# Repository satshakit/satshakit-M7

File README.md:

<div align="center"><h1 style="font-family: courier;" align="center">satshakit-M7</h1></div>

<div align="center"></div>
<div align="center"><i>An open source & fabbable STM32F7 microcontroller board.</i></div>

Premises
--
My personal objective with the development of satshakit-M7 is to bring forward the current possibilities of a Fab Lab to, locally and at cheap price, produce and customize powerful and advanced microcontroller boards, like the ones used in production. Satshakit-M7 is embedding one of the tops chips today available on the market at the time of writing (2018), aiming to represent the state of the art of what you can produce by yourself versus what you can buy. The board was made with a cheap and small milling machine and a traditional soldering station, for a total equipment price of 300€ paid once, if you mind that producing such board will cost you a lot. I personally believe that one day we will (almost) build everything we need in a Fab Lab, and satshakit-M7 wants to be a step further in that direction.

The board
--
satshakit-M7 embeds a **[Cortex M7](https://developer.arm.com/products/processors/cortex-m/cortex-m7)** microcontroller, produced by STMicroelectronics the: **[STM32F765VIT6](http://www.st.com/en/microcontrollers/stm32f765vi.html)**. Among others, the **[STM32F7](http://www.st.com/en/microcontrollers/stm32f7-series.html?querycriteria=productId=SS1858)** chip line and the Cortex-M7 architecture are including the following features:

- **32 bit** architecture
- **6-stage superscalar** pipeline with branch prediction
- dedicated **DSP** instructions
- **hardware acceleration** for graphic computation

satshakit-M7 **schematic**:

Furthermore, as the STM32 architecture and pinout are quite similar among the different STM32FXX, you could reuse the satshakit-M7 design to host other STM32F microcontrollers. Satshakit-M7 is designed to be one simple, yet complete, PCB to tryout most of the STM32F765VIT6 features and I/O. Apart from the microcontroller itself and few other small parts, the rest is having 1206 components and quite enough space to ensure an easy soldering. 

Here the main **tech specs** of satshakit-M7:

- operating frequency up to **216mhz**
- flash memory of **2MB**
- ram memory of **512KB**
- **QUAD-SPI** memory interface supporting up to 4GB of DDR external ram
- Mini **USB 2.0** full speed support with different modes (DFU,OTG,AUDIO..)
- 3 x **12bit** ADCs
- general purpose **DMA**
- camera interface up to **54MB/s**
- **4** x serials
- **4** x I2C
- **3** x CANs
- **full pinout** on board
- **HDMI-CEC**
- **LCD TFT** controller
- working voltage of **3.3V**
- cost of **21€** (buying from digi-key per single board, way less for more or from China)

satshakit-M7 **board**:

In comparison to the old **[satshakit](https://github.com/satshakit/satshakit)** based on the 328P, satshakit-M7 is several times faster and having much more memory. Here some numbers about it:

- **13.5** times higher operating frequency
- **256** times more ram memory
- **64** times more flash memory
- about **3** times more I/O pins 

Downloads
--

**downloads (right click download as):**

- [satshakit-M7 schematic](https://github.com/satshakit/satshakit-M7/raw/master/eagle/satshakit-M7/satshakit-M7.sch)
- [satshakit-M7 board](https://github.com/satshakit/satshakit-M7/raw/master/eagle/satshakit-M7/satshakit-M7.brd)
- [satshakit-M7 internal traces png](https://github.com/satshakit/satshakit-M7/raw/master/media/satshakit-M7-internal.png)
- [satshakit-M7 cutout png](https://github.com/satshakit/satshakit-M7/raw/master/media/satshakit-M7-cutout.png)
- [satshakit-M7 BOM ods](https://github.com/satshakit/satshakit-M7/raw/master/docs/satshakit-M7-BOM.ods)
- [satshakit-M7 BOM xlsx](https://github.com/satshakit/satshakit-M7/raw/master/docs/satshakit-M7-BOM.xlsx)
- [satshakit-M7 216mhz USB CubeMX example](https://github.com/satshakit/satshakit-M7/raw/master/examples/satshakit-M7-usb-216mhz.zip)
- [satshakit-M7 blink SW4STM32 example](https://github.com/satshakit/satshakit-M7/raw/master/examples/test_blink.zip)

Milling and soldering tips
--

To mill the board a **0.1mm chamfer tool** was used. I recommend to buy several of these as they could warn off  quickly, and they are very easy to be damaged (eg if you drop them). The ones from China usually lasts few cuts, better the one from USA/Europe but of course more expensive.

With such tools you should ensure to have a **flat copper sheet** and therefore also a **flat bed**. In case some parts are not milled properly you can relaunch only a specific areas by cropping subsections of the PNG. To make the board here 2 jobs were necessary. Another solution would be to launch only the job to engrave the traces of the microntroller with the 0.1mm tool, and then launch the rest with a traditional 0.4mm tool (1/64th).

Solder the microntroller by deploying an **huge amount of soldering on the sides** as shown here:

and then by removing it **using a desoldering trace**.

Make sure to **strongly solder the USB connector** to avoid that it will easily detach while connecting and disconnecting the USB cable.

Please make sure that all the **connections are fine** by using the testing function of a multimeter before powering the board. More **patience in testing** will be rewarding is then you have to trash all the board for a mistake. Also, use an **USB hub** for the first smoke test to avoid eventually damage your computer. 

Getting started with satshakit-M7
--

Find below the **satshakit-M7 pinout**:

To have a look to more functionalities associated with each pin please have into the **[STM32F765VIT6 datasheet](http://www.st.com/content/ccc/resource/technical/document/datasheet/group3/c5/37/9c/1d/a6/09/4e/1a/DM00273119/files/DM00273119.pdf/jcr:content/translations/en.DM00273119.pdf)**.

In order to program the satshakit-M7, it is recommended to use a programmer called **ST-Link v2**. You can buy the original on **[digi-key](https://www.digikey.de/product-detail/en/stmicroelectronics/ST-LINK-V2/497-10484-ND/2214535)** or a chinese clone for much less on ebay or on **[Banggood](https://www.digikey.de/product-detail/en/stmicroelectronics/ST-LINK-V2/497-10484-ND/2214535)**.

When you program the satshakit-M7, it is always recommended to:

- connect the **boot pin to the 3.3V VCC** to ensure that the programming pins are not already used for something else
- avoid to power the board from the programmer itself and connect an **external 3.3V power source**

Find here the **connection schema to program** the satshakit-M7:

To program the satshakit-M7 using the ST-Link v2 you download and install the **[STM32 ST-LINK utility ](http://www.st.com/en/development-tools/stsw-link004.html)**, which also installs the ST-Link drivers.

To program the board follow the steps below:

1. connect the satshakit-M7 following the above schema
2. connect the ST-Link to the USB of your PC
3. open the STM32 ST-LINK utility
4. click on target->connect
5. at this point if there's an error the software will warn you, in this case double check the connections and try again
6. if the connection it's ok, click on target->program
7. browse to load you binary file
8. eventually change some options, eg to verify the flash
8. press start
9. wait for the program to be uploaded
10. disconnect the board 
11. remove the boot jumper
12. power again your board

Other useful things can be found in the target menu. Try to **update your ST Link firmware** in ST_LINK->update firmware in case you have other problems in uploading the files. For more info please look at the **[STM32 ST-LINK manual](http://www.st.com/content/ccc/resource/technical/document/user_manual/65/e0/44/72/9e/34/41/8d/DM00026748.pdf/files/DM00026748.pdf/jcr:content/translations/en.DM00026748.pdf)** and the **[ST-LINK Utility manual](http://www.st.com/content/ccc/resource/technical/document/user_manual/e6/10/d8/80/d6/1d/4a/f2/CD00262073.pdf/files/CD00262073.pdf/jcr:content/translations/en.CD00262073.pdf)**.

The STM32F765VIT6 can be easiliy be configured using a graphical tool from ST, the **[STM32CubeMX](http://www.st.com/en/development-tools/stm32cubemx.html)**. Generally this is the first step to understand the main functionalities of the chips, and it's needed to generate the base code of your programs that you can later on use in your IDE. If you wish to use it, I created an **example project in the downloads: [216-USB](examples/satshakit-M7-usb-216mhz.zip)**. which you can use to run the satshakit-M7 at 216mhz and to enable the USB port in VCP mode.

When you generate the base code with STM32CubeMX, you can specify the kind of IDE you will use later to write on top of it your own code. I recommend to use the **[SW4STM32](http://www.openstm32.org/HomePage)** IDE, which is based on eclipse. I added an **example project made with this ide in the downloads: [test-blink](examples/test_blink.zip)**.

Media
--

satshakit-M7 pictures:

satshakit-M7 connected with the programmer:

satshakit-M7 with the first prototype:

satshakit-M7 blinks:

Author
--

- Daniele Ingrassia

Contact
--
- **ingrassiada@gmail.com**
- **[linkedin](http://it.linkedin.com/in/danieleingrassia)**

Thanks
--
[Fablab Kamp-Lintfort](http://fablab.hochschule-rhein-waal.de/index.php/de/)<br />
Hochschule Rhein-Waal<br />
Friedrich-Heinrich-Allee 25, 47475 Kamp-Lintfort, Germany<br />
fablab@hochschule-rhein-waal.de

License
--
This work is licensed under the terms of the open source license: Creative Commons Attribution-ShareAlike 4.0 International ([CC BY-SA 4.0](https://creativecommons.org/licenses/by-sa/4.0/)).

Disclaimer  
--

<div class="align-justify">
This hardware/software is provided "as is", and you use the hardware/software at your own risk. Under no circumstances shall any author be liable for direct, indirect, special, incidental, or consequential damages resulting from the use, misuse, or inability to use this hardware/software, even if the authors have been advised of the possibility of such damages.</div>

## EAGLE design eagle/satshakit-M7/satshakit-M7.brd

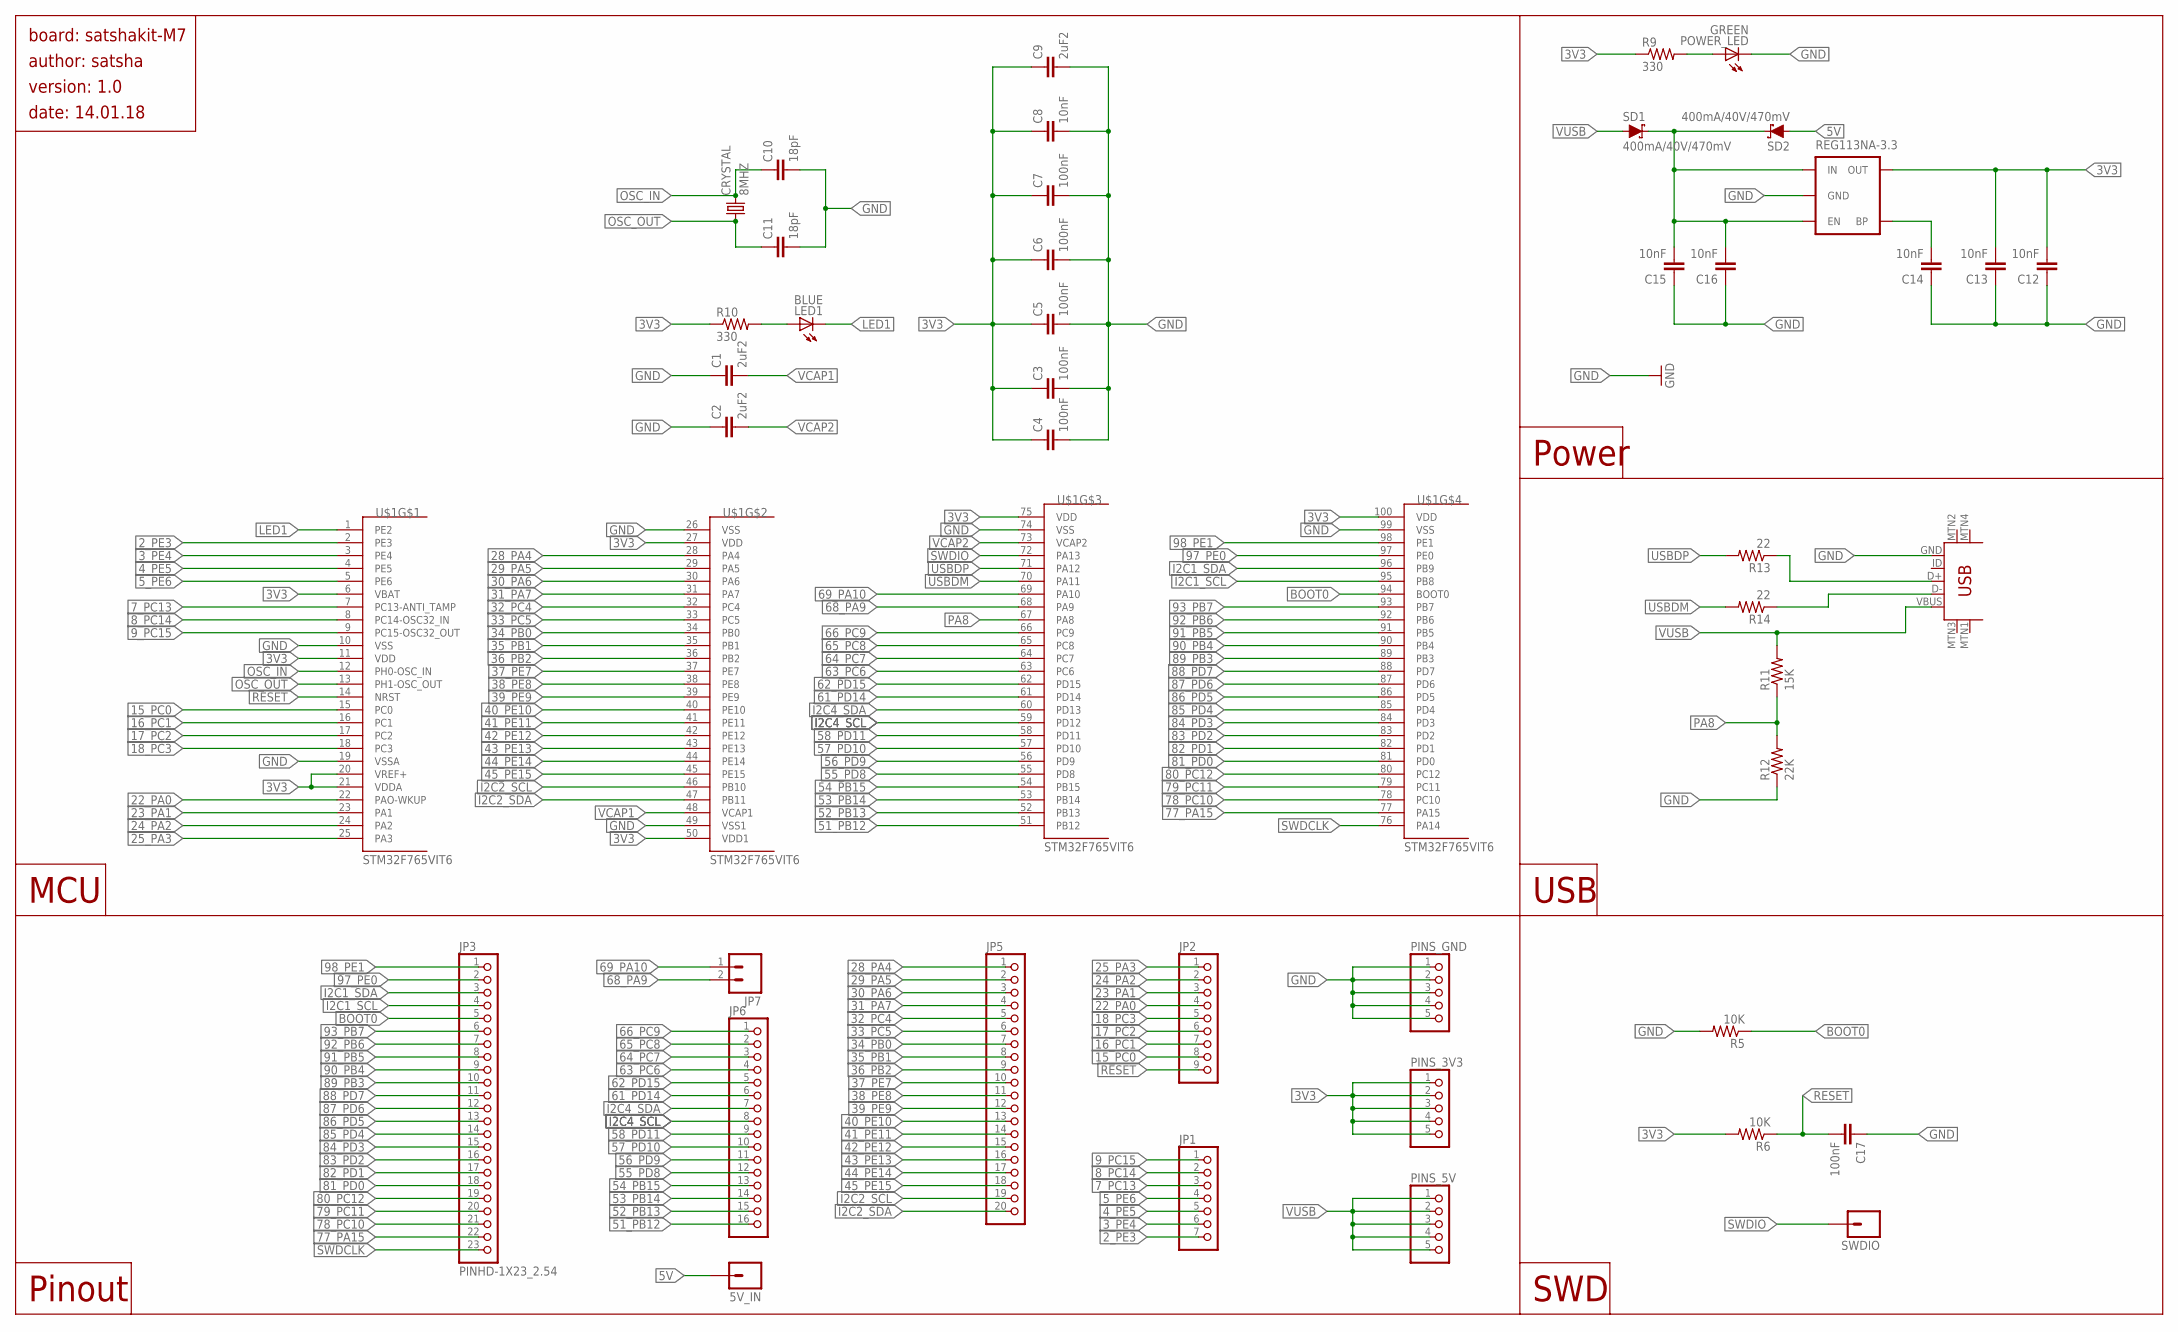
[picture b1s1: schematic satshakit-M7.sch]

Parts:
5V_IN: M01PTH_LONGPAD; 1X01_LONGPAD
C1, C2, C9: 2uF2; 1206
C3, C4, C5, C6, C7, C17: 100nF; 1206
C8, C12, C13, C14, C15, C16: 10nF; 1206
C10, C11: 18pF; 1206
CRYSTAL: 8MHZ; CSM-7X-DU
JP1: PINHD-1X07_2.54; 1X07
JP2: PINHD-1X09_2.54; 1X09
JP3: PINHD-1X23_2.54; 1X23
JP5: PINHD-1X20_2.54; 1X20
JP6: PINHD-1X16_2.54; 1X16
JP7: M02; 1X02_LONGPADS
LED1: BLUE; 1206
PINS_3V3, PINS_5V: PINHD-1X05_2.54; 1X05
PINS_GND: PINHD-1X05_2.54; 1X05
POWER_LED: GREEN; 1206
R5, R6: 10K; 1206
R9, R10: 330; 1206
R11: 15K; 1206
R12: 22K; 1206
R13, R14: 22; 1206
REG113NA-3.3: V_REG_LDOSMD; SOT23-5
SD1, SD2: 400mA/40V/470mV; SOT23-3
SWDIO: M01PTH_LONGPAD; 1X01_LONGPAD
U$1: STM32F765VIT6; LQFP100
U$7: USB-MINIB-5PIN; USB-MINIB

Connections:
2_PE3: JP1.7, U$1.2 (PE3)
3V3: C3.1, C4.1, C5.1, C6.1, C7.1, C8.1, C9.1, C12.2, C13.2, PINS_3V3.1, PINS_3V3.2, PINS_3V3.3, PINS_3V3.4, PINS_3V3.5, R6.2, R9.1, R10.1, REG113NA-3.3.5 (OUT), U$1.6 (VBAT), U$1.11 (VDD), U$1.20 (VREF+), U$1.21 (VDDA), U$1.27 (VDD), U$1.50 (VDD1), U$1.75 (VDD), U$1.100 (VDD)
3_PE4: JP1.6, U$1.3 (PE4)
4_PE5: JP1.5, U$1.4 (PE5)
5V: 5V_IN.1, SD2.1 (A)
5_PE6: JP1.4, U$1.5 (PE6)
7_PC13: JP1.3, U$1.7 (PC13-ANTI_TAMP)
8_PC14: JP1.2, U$1.8 (PC14-OSC32_IN)
9_PC15: JP1.1, U$1.9 (PC15-OSC32_OUT)
15_PC0: JP2.8, U$1.15 (PC0)
16_PC1: JP2.7, U$1.16 (PC1)
17_PC2: JP2.6, U$1.17 (PC2)
18_PC3: JP2.5, U$1.18 (PC3)
22_PA0: JP2.4, U$1.22 (PAO-WKUP)
23_PA1: JP2.3, U$1.23 (PA1)
24_PA2: JP2.2, U$1.24 (PA2)
25_PA3: JP2.1, U$1.25 (PA3)
28_PA4: JP5.1, U$1.28 (PA4)
29_PA5: JP5.2, U$1.29 (PA5)
30_PA6: JP5.3, U$1.30 (PA6)
31_PA7: JP5.4, U$1.31 (PA7)
32_PC4: JP5.5, U$1.32 (PC4)
33_PC5: JP5.6, U$1.33 (PC5)
34_PB0: JP5.7, U$1.34 (PB0)
35_PB1: JP5.8, U$1.35 (PB1)
36_PB2: JP5.9, U$1.36 (PB2)
37_PE7: JP5.10, U$1.37 (PE7)
38_PE8: JP5.11, U$1.38 (PE8)
39_PE9: JP5.12, U$1.39 (PE9)
40_PE10: JP5.13, U$1.40 (PE10)
41_PE11: JP5.14, U$1.41 (PE11)
42_PE12: JP5.15, U$1.42 (PE12)
43_PE13: JP5.16, U$1.43 (PE13)
44_PE14: JP5.17, U$1.44 (PE14)
45_PE15: JP5.18, U$1.45 (PE15)
51_PB12: JP6.16, U$1.51 (PB12)
52_PB13: JP6.15, U$1.52 (PB13)
53_PB14: JP6.14, U$1.53 (PB14)
54_PB15: JP6.13, U$1.54 (PB15)
55_PD8: JP6.12, U$1.55 (PD8)
56_PD9: JP6.11, U$1.56 (PD9)
57_PD10: JP6.10, U$1.57 (PD10)
58_PD11: JP6.9, U$1.58 (PD11)
61_PD14: JP6.6, U$1.61 (PD14)
62_PD15: JP6.5, U$1.62 (PD15)
63_PC6: JP6.4, U$1.63 (PC6)
64_PC7: JP6.3, U$1.64 (PC7)
65_PC8: JP6.2, U$1.65 (PC8)
66_PC9: JP6.1, U$1.66 (PC9)
68_PA9: JP7.2, U$1.68 (PA9)
69_PA10: JP7.1, U$1.69 (PA10)
77_PA15: JP3.22, U$1.77 (PA15)
78_PC10: JP3.21, U$1.78 (PC10)
79_PC11: JP3.20, U$1.79 (PC11)
80_PC12: JP3.19, U$1.80 (PC12)
81_PD0: JP3.18, U$1.81 (PD0)
82_PD1: JP3.17, U$1.82 (PD1)
83_PD2: JP3.16, U$1.83 (PD2)
84_PD3: JP3.15, U$1.84 (PD3)
85_PD4: JP3.14, U$1.85 (PD4)
86_PD5: JP3.13, U$1.86 (PD5)
87_PD6: JP3.12, U$1.87 (PD6)
88_PD7: JP3.11, U$1.88 (PD7)
89_PB3: JP3.10, U$1.89 (PB3)
90_PB4: JP3.9, U$1.90 (PB4)
91_PB5: JP3.8, U$1.91 (PB5)
92_PB6: JP3.7, U$1.92 (PB6)
93_PB7: JP3.6, U$1.93 (PB7)
97_PE0: JP3.2, U$1.97 (PE0)
98_PE1: JP3.1, U$1.98 (PE1)
BOOT0: JP3.5, R5.1, U$1.94 (BOOT0)
GND: C1.1, C2.1, C3.2, C4.2, C5.2, C6.2, C7.2, C8.2, C9.2, C10.2, C11.2, C12.1, C13.1, C14.1, C15.1, C16.1, C17.1, PINS_GND.1, PINS_GND.2, PINS_GND.3, PINS_GND.4, PINS_GND.5, POWER_LED.2 (C), R5.2, R12.1, REG113NA-3.3.2 (GND), U$1.10 (VSS), U$1.19 (VSSA), U$1.26 (VSS), U$1.49 (VSS1), U$1.74 (VSS), U$1.99 (VSS), U$7.GND
I2C1_SCL: JP3.4, U$1.95 (PB8)
I2C1_SDA: JP3.3, U$1.96 (PB9)
I2C2_SCL: JP5.19, U$1.46 (PB10)
I2C2_SDA: JP5.20, U$1.47 (PB11)
I2C4_SCL: JP6.8, U$1.59 (PD12)
I2C4_SDA: JP6.7, U$1.60 (PD13)
LED1: LED1.2 (C), U$1.1 (PE2)
unnamed: POWER_LED.1 (A), R9.2
unnamed: LED1.1 (A), R10.2
unnamed: C15.2, C16.2, REG113NA-3.3.1 (IN), REG113NA-3.3.3 (EN), SD1.3 (C), SD2.3 (C)
unnamed: R14.1, U$7.D-
unnamed: R13.1, U$7.D+
NR: C14.2, REG113NA-3.3.4 (BP)
OSC_IN: C10.1, CRYSTAL.2, U$1.12 (PH0-OSC_IN)
OSC_OUT: C11.1, CRYSTAL.1, U$1.13 (PH1-OSC_OUT)
PA8: R11.1, R12.2, U$1.67 (PA8)
RESET: C17.2, JP2.9, R6.1, U$1.14 (NRST)
SWDCLK: JP3.23, U$1.76 (PA14)
SWDIO: SWDIO.1, U$1.72 (PA13)
USBDM: R14.2, U$1.70 (PA11)
USBDP: R13.2, U$1.71 (PA12)
VCAP1: C1.2, U$1.48 (VCAP1)
VCAP2: C2.2, U$1.73 (VCAP2)
VUSB: PINS_5V.1, PINS_5V.2, PINS_5V.3, PINS_5V.4, PINS_5V.5, R11.2, SD1.1 (A), U$7.VBUS

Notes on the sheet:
Power
USB
SWD
Pinout
MCU
board: satshakit-M7
author: satsha
version: 1.0
date: 14.01.18

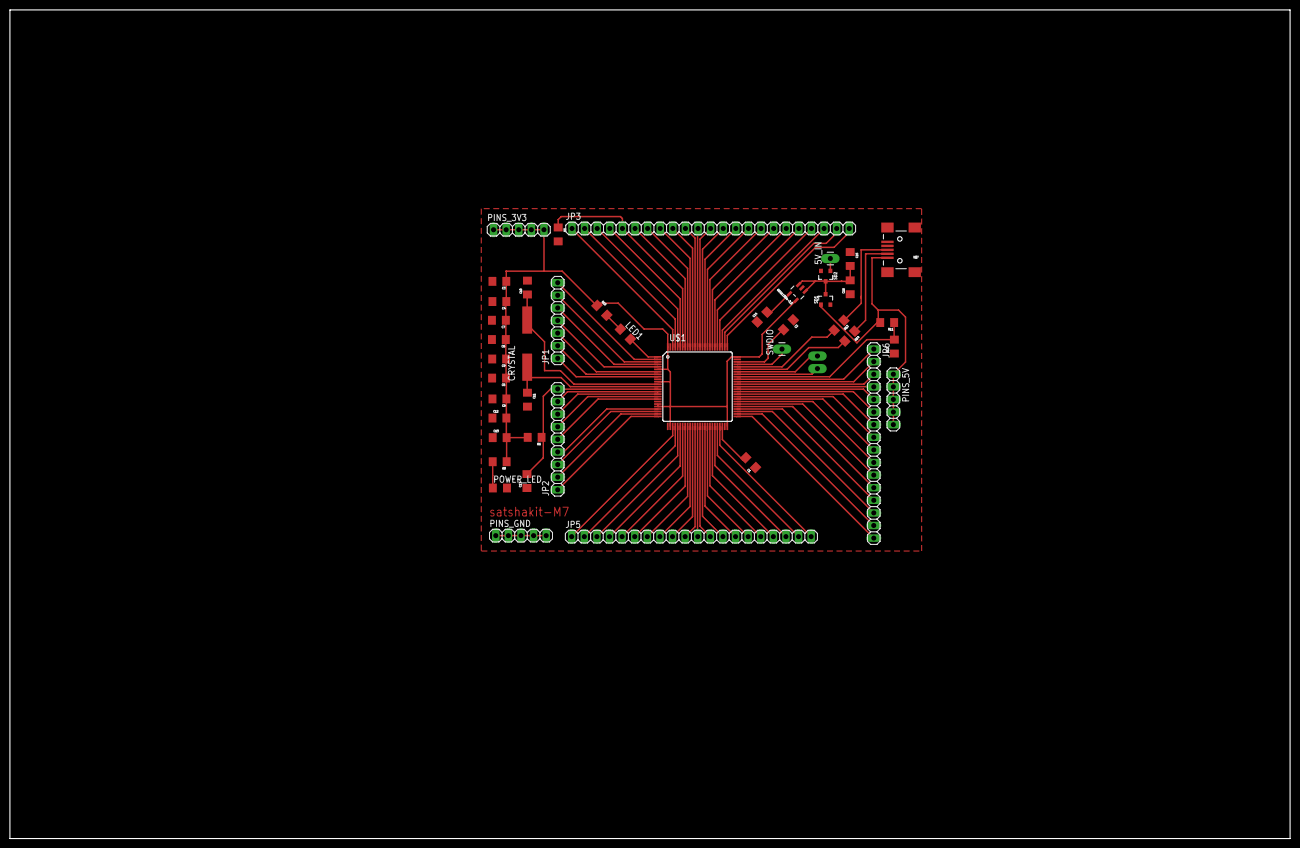
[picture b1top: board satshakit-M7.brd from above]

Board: 2 copper layers, 258.0 x 167.0 mm, 44 parts (0 on the bottom side), 96 nets.

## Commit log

2018-01-17 satshakit-M7
2018-01-17 readme fixes
2018-01-17 fixed gifs
2018-01-17 fixed links
2018-01-19 readme fixes
    readme fixes
2018-01-19 fixed example
2020-05-31 license change

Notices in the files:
parts and their libraries:
01_SparkFun: Licensing: CC v3.0 Share-Alike You are welcome to use this library for commercial purposes.
SparkFun-DiscreteSemi: Licensing: Creative Commons ShareAlike 4.0 International - https://creativecommons.org/licenses/by-sa/4.0
